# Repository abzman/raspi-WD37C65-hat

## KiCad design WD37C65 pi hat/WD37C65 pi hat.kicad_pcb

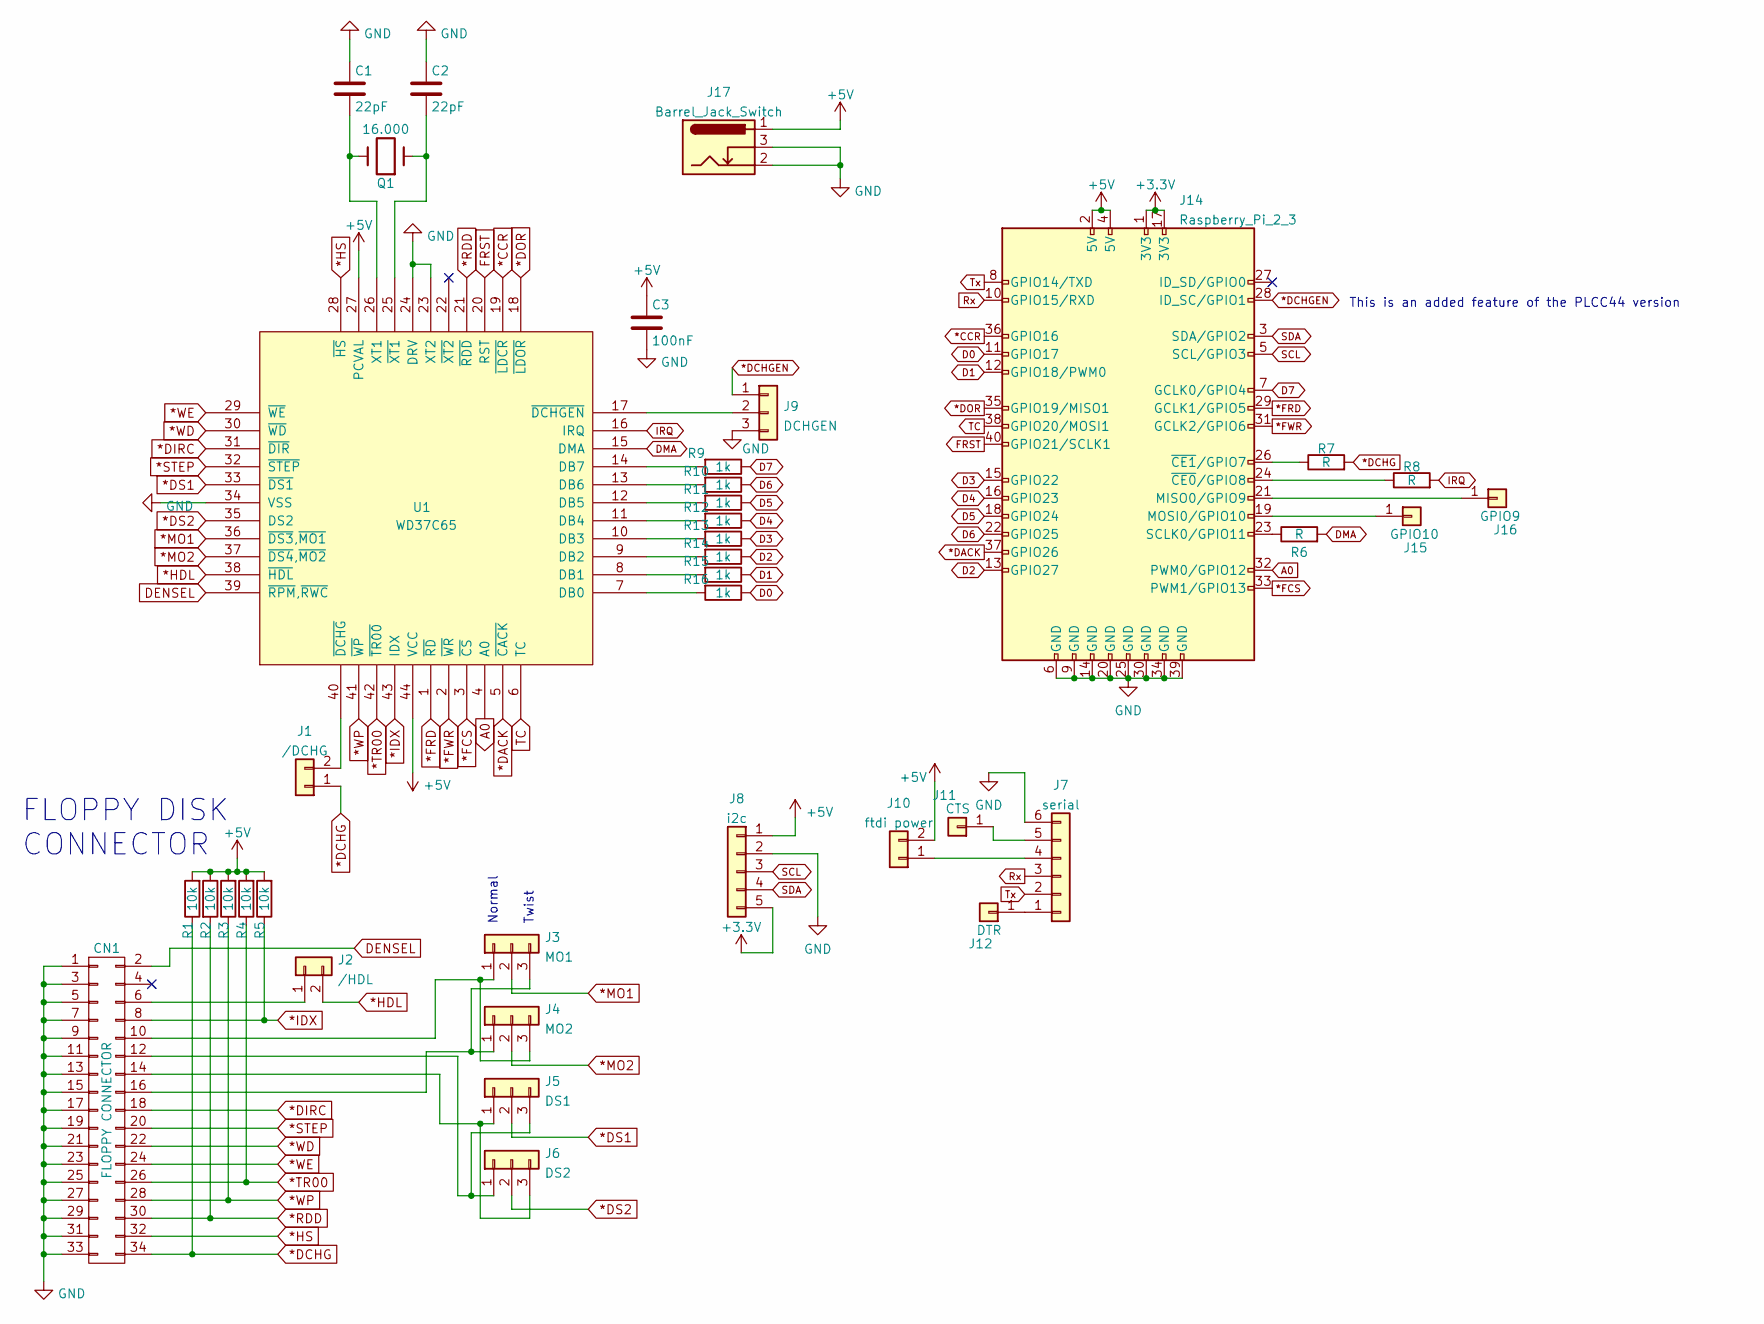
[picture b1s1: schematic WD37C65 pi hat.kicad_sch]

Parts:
C1, C2: 22pF; C_0603_1608Metric
C3: 100nF; C_0603_1608Metric
CN1: FLOPPY CONNECTOR; PinHeader_2x17_P2.54mm_Vertical
J1: /DCHG; PinHeader_1x02_P2.54mm_Vertical
J2: /HDL; PinHeader_1x02_P2.54mm_Vertical
J3: MO1; SolderJumper-3_P2.0mm_Open_TrianglePad1.0x1.5mm_NumberLabels
J4: MO2; SolderJumper-3_P2.0mm_Open_TrianglePad1.0x1.5mm_NumberLabels
J5: DS1; SolderJumper-3_P2.0mm_Open_TrianglePad1.0x1.5mm_NumberLabels
J6: DS2; SolderJumper-3_P2.0mm_Open_TrianglePad1.0x1.5mm_NumberLabels
J7: serial; PinHeader_1x06_P2.54mm_Horizontal
J8: i2c; PinHeader_1x05_P2.54mm_Vertical
J9: DCHGEN; PinHeader_1x03_P2.54mm_Vertical
J10: ftdi power; PinHeader_1x02_P2.54mm_Vertical
J11: CTS; PinHeader_1x01_P2.54mm_Vertical
J12: DTR; PinHeader_1x01_P2.54mm_Vertical
J14: Raspberry_Pi_2_3; PinHeader_2x20_P2.54mm_Vertical
J15: GPIO10; PinHeader_1x01_P2.54mm_Vertical
J16: GPIO9; PinHeader_1x01_P2.54mm_Vertical
J17: Barrel_Jack_Switch; BarrelJack_Horizontal
Q1: 16.000; Crystal_HC49-U_Vertical
R1, R2, R3, R4, R5: 10k; R_0603_1608Metric
R6, R7, R8: R; R_0603_1608Metric
R9, R10, R11, R12, R13, R14, R15, R16: 1k; R_0603_1608Metric
U1: WD37C65; PLCC-44

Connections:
*CCR: J14.36 (GPIO16), U1.19 (~LDCR)
*DACK: J14.37 (GPIO26), U1.5 (~CACK)
*DCHG: CN1.34, J1.1, R1.1, R7.2
*DCHGEN: J9.1, J14.28 (ID_SC/GPIO1)
*DIRC: CN1.18, U1.31 (~DIR)
*DOR: J14.35 (GPIO19/MISO1), U1.18 (~LDOR)
*DS1: J5.2, U1.33 (~DS1)
*DS2: J6.2, U1.35 (DS2)
*FCS: J14.33 (PWM1/GPIO13), U1.3 (~CS)
*FRD: J14.29 (GCLK1/GPIO5), U1.1 (~RD)
*FWR: J14.31 (GCLK2/GPIO6), U1.2 (~WR)
*HDL: J2.2, U1.38 (~HDL)
*HS: CN1.32, U1.28 (~HS)
*IDX: CN1.8, R5.1, U1.43 (IDX)
*MO1: J3.2, U1.36 (~DS3,~MO1)
*MO2: J4.2, U1.37 (~DS4,~MO2)
*RDD: CN1.30, R2.2, U1.21 (~RDD)
*STEP: CN1.20, U1.32 (~STEP)
*TR00: CN1.26, R4.1, U1.42 (~TR00)
*WD: CN1.22, U1.30 (~WD)
*WE: CN1.24, U1.29 (~WE)
*WP: CN1.28, R3.1, U1.41 (~WP)
+3V3: J8.5, J14.1 (3V3), J14.17 (3V3)
+5V: C3.1, J8.1, J10.2, J14.2 (5V), J14.4 (5V), J17.1, R1.2, R2.1, R3.2, R4.2, R5.2, U1.27 (PCVAL), U1.44 (VCC)
A0: J14.32 (PWM0/GPIO12), U1.4 (A0)
D0: J14.11 (GPIO17), R16.1
D1: J14.12 (GPIO18/PWM0), R15.1
D2: J14.13 (GPIO27), R14.1
D3: J14.15 (GPIO22), R13.1
D4: J14.16 (GPIO23), R12.1
D5: J14.18 (GPIO24), R11.1
D6: J14.22 (GPIO25), R10.1
D7: J14.7 (GCLK0/GPIO4), R9.1
DENSEL: CN1.2, U1.39 (~RPM,~RWC)
DMA: R6.2, U1.15 (DMA)
FRST: J14.40 (GPIO21/SCLK1), U1.20 (RST)
GND: C1.1, C2.1, C3.2, CN1.1, CN1.3, CN1.5, CN1.7, CN1.9, CN1.11, CN1.13, CN1.15, CN1.17, CN1.19, CN1.21, CN1.23, CN1.25, CN1.27, CN1.29, CN1.31, CN1.33, J7.6, J8.2, J9.3, J14.6 (GND), J14.9 (GND), J14.14 (GND), J14.20 (GND), J14.25 (GND), J14.30 (GND), J14.34 (GND), J14.39 (GND), J17.2, J17.3, U1.23 (XT2), U1.24 (DRV), U1.34 (VSS)
IRQ: R8.2, U1.16 (IRQ)
unnamed: C1.2, Q1.2, U1.26 (XT1)
unnamed: C2.2, Q1.1, U1.25 (~XT1)
unnamed: CN1.6, J2.1
unnamed: CN1.10, J3.1, J4.3
unnamed: CN1.12, J5.3, J6.1
unnamed: CN1.14, J5.1, J6.3
unnamed: CN1.16, J3.3, J4.1
unnamed: J1.2, U1.40 (~DCHG)
unnamed: J9.2, U1.17 (~DCHGEN)
unnamed: J7.4, J10.1
unnamed: J7.5, J11.1
unnamed: J7.1, J12.1
unnamed: J14.19 (MOSI0/GPIO10), J15.1
unnamed: J14.21 (MISO0/GPIO9), J16.1
unnamed: J14.23 (SCLK0/GPIO11), R6.1
unnamed: J14.24 (~CE0/GPIO8), R8.1
unnamed: J14.26 (~CE1/GPIO7), R7.1
unnamed: R9.2, U1.14 (DB7)
unnamed: R10.2, U1.13 (DB6)
unnamed: R11.2, U1.12 (DB5)
unnamed: R12.2, U1.11 (DB4)
unnamed: R13.2, U1.10 (DB3)
unnamed: R14.2, U1.9 (DB2)
unnamed: R15.2, U1.8 (DB1)
unnamed: R16.2, U1.7 (DB0)
Rx: J7.3, J14.10 (GPIO15/RXD)
SCL: J8.3, J14.5 (SCL/GPIO3)
SDA: J8.4, J14.3 (SDA/GPIO2)
TC: J14.38 (GPIO20/MOSI1), U1.6 (TC)
Tx: J7.2, J14.8 (GPIO14/TXD)

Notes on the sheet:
FLOPPY DISK CONNECTOR
Normal
Twist
This is an added feature of the PLCC44 version

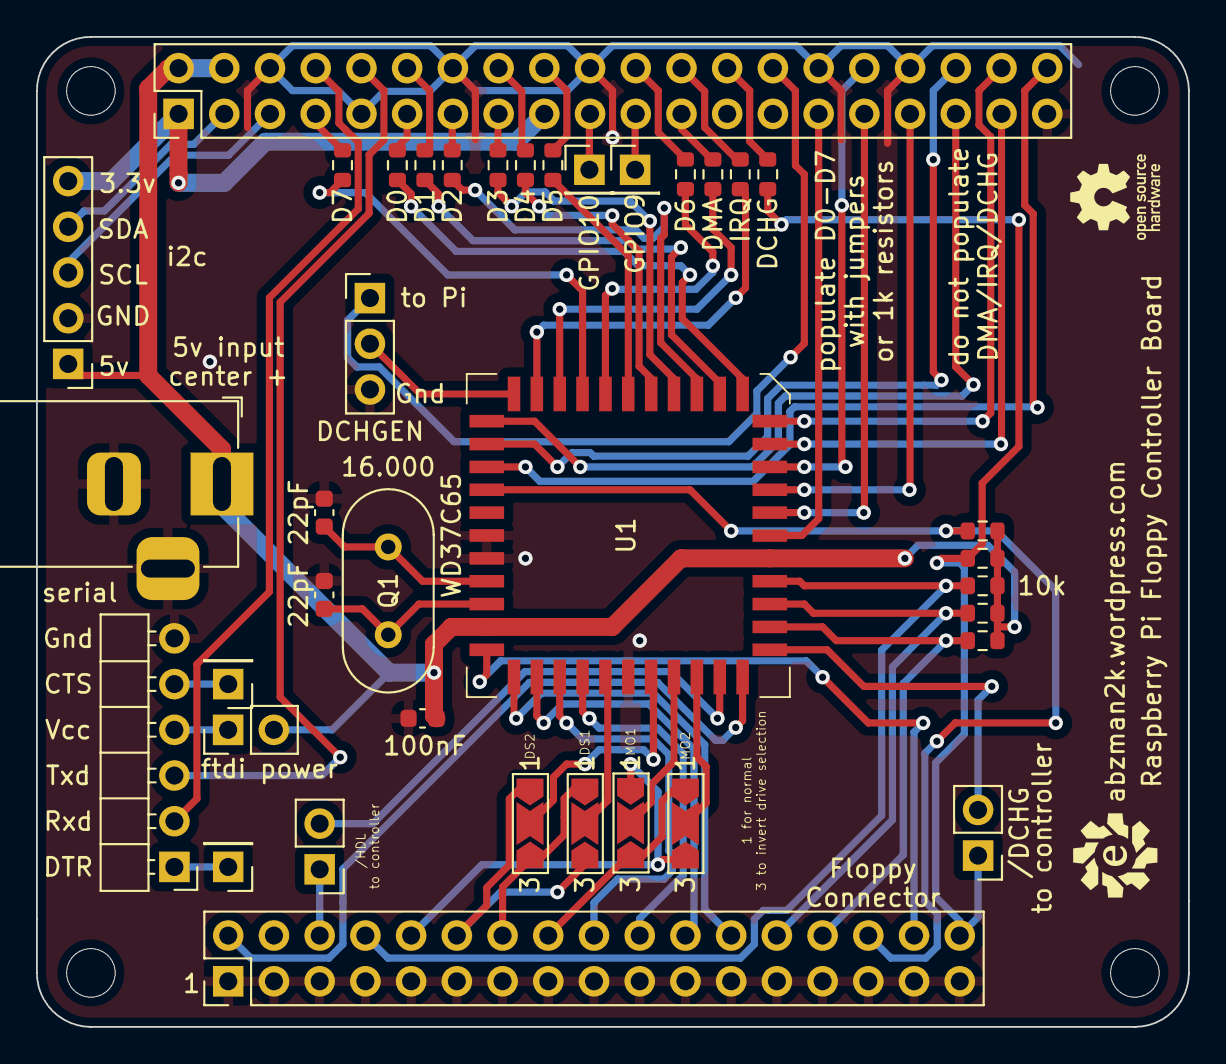
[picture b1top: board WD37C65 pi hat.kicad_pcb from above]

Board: 2 copper layers, 64.0 x 55.0 mm, 38 parts (0 on the bottom side), 68 nets.

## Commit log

2022-04-18 first layout
2022-08-20 added gerbers, ERC DRC fixes
2022-11-25 added gitignore
2024-01-18 tweaked project file
